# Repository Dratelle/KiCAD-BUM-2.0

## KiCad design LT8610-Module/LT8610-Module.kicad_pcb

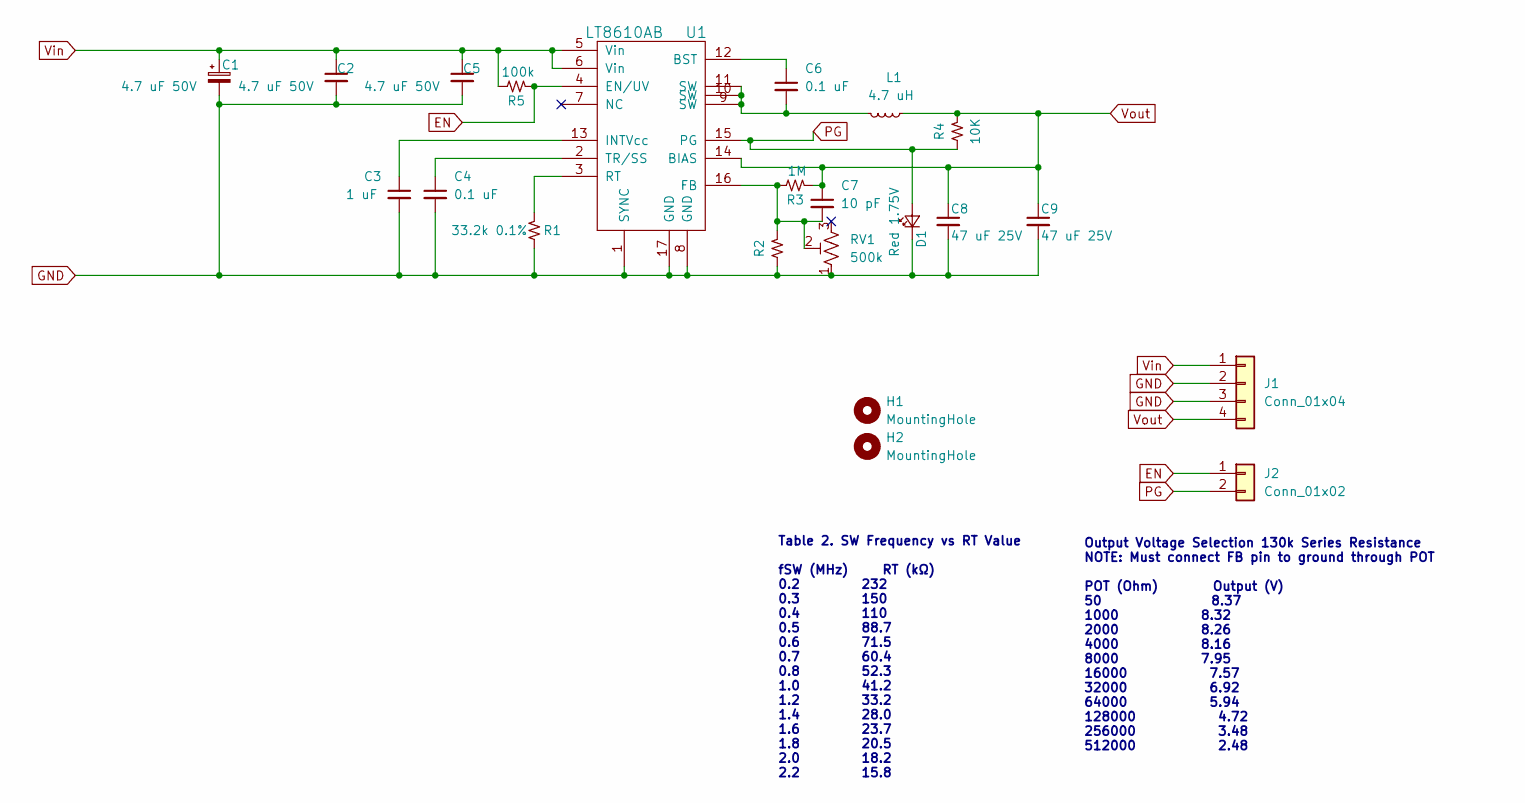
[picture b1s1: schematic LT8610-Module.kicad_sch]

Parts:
C1: 4.7 uF 50V; CP_Elec_4x5.4; Part Number PCE3931CT-ND
C2, C5: 4.7 uF 50V; C_0805_2012Metric; Part Number 490-GRM21BZ71H475KE15KCT-ND
C3: 1 uF; C_0603_1608Metric; Part Number 13-CC0603KRX6S8BB105CT-ND
C4, C6: 0.1 uF; C_0402_1005Metric; Part Number 445-5933-1-ND
C7: 10 pF; C_0402_1005Metric; Part Number 399-C0402C100K5RAC7867CT-ND
C8, C9: 47 uF 25V; C_1206_3216Metric; Part Number 445-8047-1-ND
D1: Red 1.75V; LED_0402_1005Metric; Part Number 1080-1571-1-ND
H1, H2: MountingHole; MountingHole_2.2mm_M2_ISO7380
J1: Conn_01x04; PinHeader_1x04_P2.54mm_Vertical
J2: Conn_01x02; PinHeader_1x02_P2.54mm_Vertical
L1: 4.7 uH; L_Vishay_IHLP-2020; Part Number 541-1090-1-ND
R1: 33.2k 0.1%; R_0402_1005Metric; Part Number A127465CT-ND
R2: R_0402_1005Metric
R3: 1M; R_0402_1005Metric; Part Number 13-RE0402BRE071MLCT-ND
R4: 10K; R_0402_1005Metric; Part Number TNP10.0KDACT-ND
R5: 100k; R_0402_1005Metric; Part Number A102574CT-ND
RV1: 500k; Potentiometer_Bourns_3214W_Vertical; Part Number 3214W-1-504ECT-ND
U1: LT8610AB; MSOP-16-1EP_3x4mm_P0.5mm_EP1.65x2.85mm_ThermalVias; Part Number LT8610ABHMSE#PBF-ND

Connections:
EN: J2.1, R5.1, U1.4 (EN/UV)
GND: C1.2, C2.2, C3.2, C4.2, C5.2, C8.2, C9.2, D1.1 (K), J1.2, J1.3, R1.2, R2.2, RV1.1, U1.1 (SYNC), U1.8 (GND), U1.17 (GND)
unnamed: C3.1, U1.13 (INTVcc)
unnamed: C4.1, U1.2 (TR/SS)
unnamed: C6.1, U1.12 (BST)
unnamed: C6.2, L1.2, U1.9 (SW), U1.10 (SW), U1.11 (SW)
unnamed: C7.2, R2.1, R3.2, RV1.2, U1.16 (FB)
unnamed: R1.1, U1.3 (RT)
PG: D1.2 (A), J2.2, R4.2, U1.15 (PG)
Vin: C1.1, C2.1, C5.1, J1.1, R5.2, U1.5 (Vin), U1.6 (Vin)
Vout: C7.1, C8.1, C9.1, J1.4, L1.1, R3.1, R4.1, U1.14 (BIAS)

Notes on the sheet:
Table 2. SW Frequency vs RT Value fSW (MHz) RT (kΩ) 0.2 232 0.3 150 0.4 110 0.5 88.7 0.6 71.5 0.7 60.4 0.8 52.3 1.0 41.2 1.2 33.2 1.4 28.0 1.6 23.7 1.8 20.5 2.0 18.2 2.2 15.8
Output Voltage Selection 130k Series Resistance NOTE: Must connect FB pin to ground through POT POT (Ohm) Output (V) 50 8.37 1000 8.32 2000 8.26 4000 8.16 8000 7.95 16000 7.57 32000 6.92 64000 5.94 128000 4.72 256000 3.48 512000 2.48

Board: 4 copper layers, 22 parts (0 on the bottom side), 11 nets, no tracks yet.

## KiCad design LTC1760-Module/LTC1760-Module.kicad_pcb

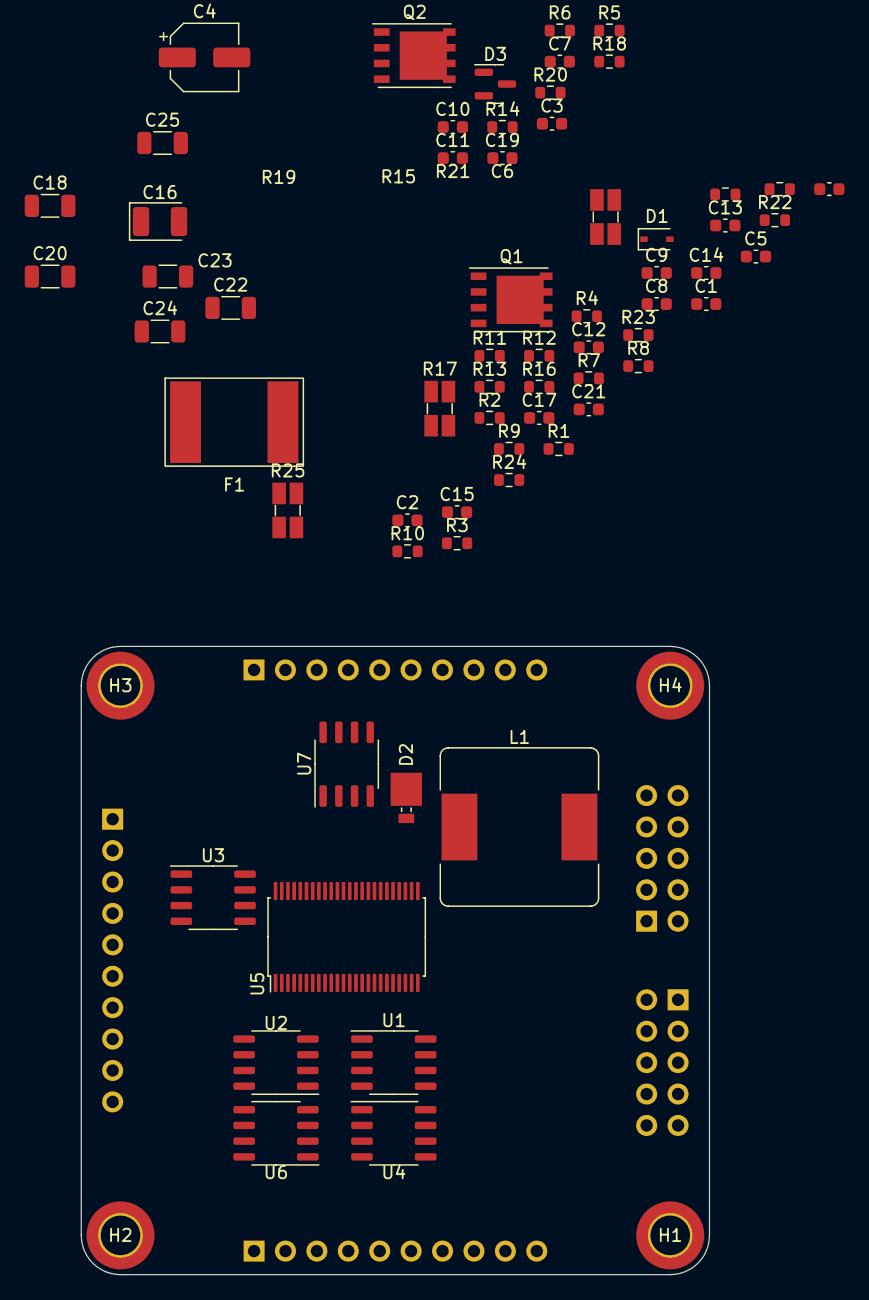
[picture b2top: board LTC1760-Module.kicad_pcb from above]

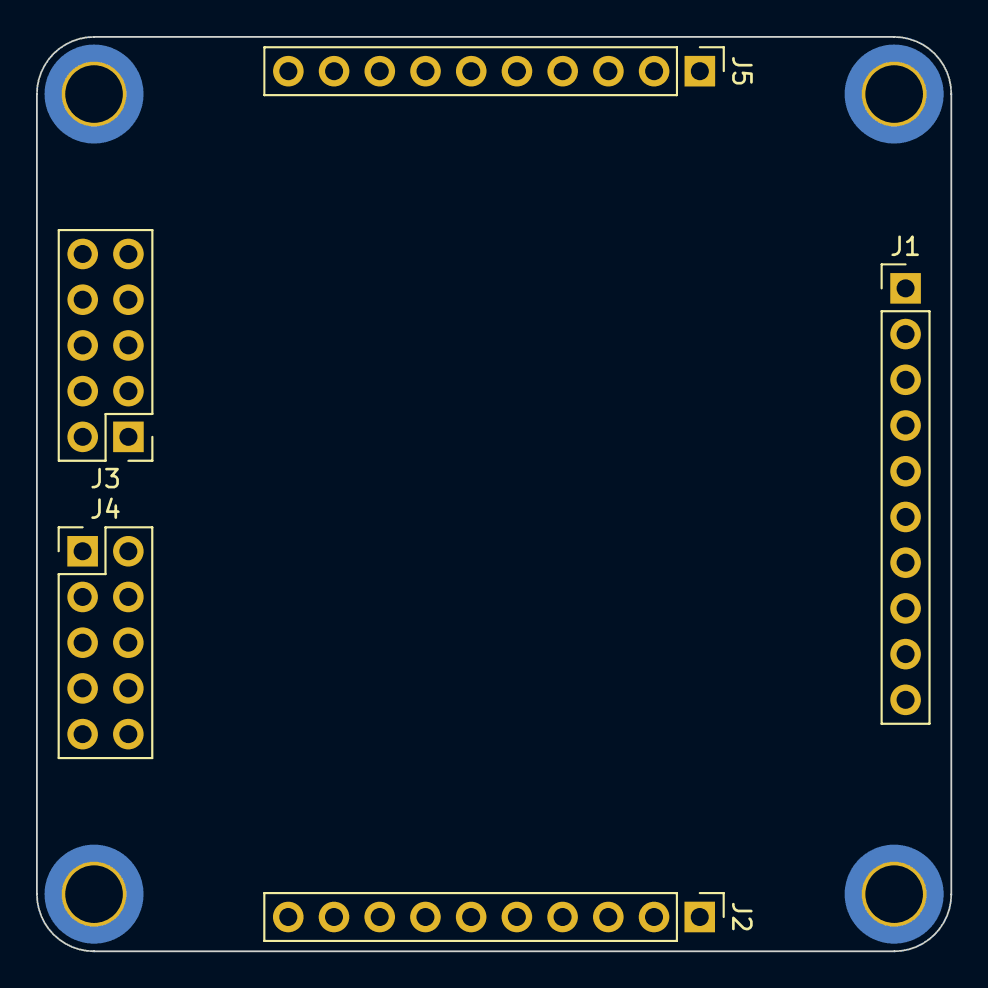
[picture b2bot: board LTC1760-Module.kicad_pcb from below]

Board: 2 copper layers, 50.8 x 50.8 mm, 73 parts (5 on the bottom side), 67 nets, no tracks yet.

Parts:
C1: 0.12uF; C_0603_1608Metric
C2, C8, C21: 100pF; C_0603_1608Metric
C3, C5, C7, C9, C12, C13, C15, C19: 0.1uF; C_0603_1608Metric
C4: 10 uF 50V; CP_Elec_5x5.3
C6: 1uF; C_0603_1608Metric
C10: 0.012uF; C_0603_1608Metric
C11: 1800pF; C_0603_1608Metric
C14: 0.47 uF; C_0603_1608Metric
C16: 4.7uF; CP_EIA-3528-15_AVX-H
C17: 0.22 uF; C_0603_1608Metric
C18, C20, C22, C23, C24, C25: 10uF; C_1206_3216Metric
D1: CMDSH-3; D_SOD-323
D2: MBRM140T3; D_Powermite_AK
D3: BAT54A; SOT-23
F1: 3A 36V; MF-GSMF
H1, H2, H3, H4: MountingHole_Pad; MountingHole_3.2mm_M3_ISO14580_Pad_TopBottom
J1, J2: Battery 1; PinHeader_1x10_P2.54mm_Vertical
J3: Parallel-I/O; PinHeader_2x05_P2.54mm_Vertical
J4: System-I/O; PinHeader_2x05_P2.54mm_Vertical
J5: Power-I/O; PinHeader_1x10_P2.54mm_Vertical
L1: 10 uH; L_Bourns_SRR1260
Q1, Q2: Si7141DP; PowerPAK_SO-8_Single
R1: 3.3k 1%; R_0603_1608Metric
R2, R4, R6: 15k 1%; R_0603_1608Metric
R3: 47 1%; R_0603_1608Metric
R5, R18: 100 1%; R_0603_1608Metric
R7: 1.21k 1%; R_0603_1608Metric
R8: 51k 1%; R_0603_1608Metric
R9: 12.7k 1%; R_0603_1608Metric
R10, R12: 54.9k 1%; R_0603_1608Metric
R11, R13: 1.13k 1%; R_0603_1608Metric
R14: 4.99k 1%; R_0603_1608Metric
R15, R16: 510k 1%; R_0603_1608Metric
R17: 0.033 1%; Ohmite_LVK12_1234
R19: 0.012 1%; Ohmite_LVK12_1234
R20, R22: 34k 1% 0603; R_0603_1608Metric
R21: 10k 1% 0603; R_0603_1608Metric
R23: 1k 1%; R_0603_1608Metric
R24: 280k 1%; R_0603_1608Metric
R25: 0.024 1%; Ohmite_LVK12_1234
U1, U2, U7: FDS6990; SO-8_3.9x4.9mm_P1.27mm
U3, U4, U6: FDS4935BZ; SO-8_3.9x4.9mm_P1.27mm
U5: LTC1760; TSSOP-48_6.1x12.5mm_P0.5mm

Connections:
/CHG_OUT: C24.1, C25.1, R25.4, U1.5 (D), U1.6 (D), U1.7 (D), U1.8 (D)
/CLP: C12.2, J3.6, R14.1, U5.36 (CLP)
/DCDIV: C8.1, J3.5, R7.2, R9.1, U5.16 (DCDIV)
/DCOUT: J5.4, J5.5, J5.6
/DCSUM: R19.4, U3.5 (D), U3.6 (D), U4.5 (D), U4.6 (D), U4.7 (D), U4.8 (D)
/DCSUPPLY: C22.1, C23.1, R17.4, U3.7 (D), U3.8 (D), U7.7 (D), U7.8 (D)
/GND: C1.2, C2.2, C3.2, C4.2, C5.1, C6.2, C7.1, C8.2, C9.2, C10.2, C11.2, C13.1, C14.2, C16.2, C18.2, C19.1, C20.2, C21.2, C22.2, C23.2, C24.2, C25.2, D2.2 (A), H1.1, H2.1, H3.1, H4.1, J1.9, J1.10, J2.9, J2.10, J3.9, J3.10, J4.9, J4.10, J5.7, J5.8, J5.9, J5.10, R7.1, R20.1, R21.1, R22.1, U5.24 (GND), U5.38 (PGND), U7.3 (S)
/ILIMT: R21.2, U5.32 (ILIM)
/INTB: R6.2, U5.29 (INTB)
/LOPWR: C21.1, R20.2, R24.1, U5.12 (LOPWR)
/MODE: C5.2, J3.3, J3.4, R2.1, R3.1, R4.1, R6.1, U5.20 (VDDS), U5.25 (VCC2), U5.26 (MODE)
/SCL: J4.3, R4.2, U5.18 (SCL)
/SCL_B1: J1.3, J1.4, J4.5, U5.19 (SCL_B1)
/SCL_B2: J2.3, J2.4, J4.7, U5.17 (SCL_B2)
/SCN: J3.8, R19.2, U5.4 (SCN)
/SCP: J3.7, R19.3, U5.5 (SCP)
/SDA: J4.4, R2.2, U5.22 (SDA)
/SDA_B1: J1.5, J1.6, J4.6, U5.23 (SDA_B1)
/SDA_B2: J2.5, J2.6, J4.8, U5.21 (SDA_B2)
/TH1A: R11.2, U5.30 (TH1A)
/TH1B: R10.2, U5.31 (TH1B)
/TH2A: R13.2, U5.28 (TH2A)
/TH2B: R12.2, U5.27 (TH2B)
/VCC: C16.1, C19.2, D1.2 (A), J3.2, R3.2, R23.2, U5.40 (VCC)
/VLIM: R22.2, U5.33 (VLIM)
/VPLUS: C6.1, J3.1, R5.2
/V_B1: D3.1, Q1.5 (D), U2.7 (D), U2.8 (D), U5.3 (BAT1), U6.5 (D), U6.6 (D)
/V_B2: D3.2, Q2.5 (D), U2.5 (D), U2.6 (D), U5.2 (BAT2), U6.7 (D), U6.8 (D)
/Vin: C4.1, C7.2, J5.1, J5.2, J5.3, R9.2, R17.1
/~BAT_EN1: J4.1, J4.2, Q1.4 (G), R15.2
/~BAT_EN2: Q2.4 (G), R16.2
unnamed: C1.1, R1.2
unnamed: C2.1, R1.1, U5.14 (ITH)
unnamed: C3.1, U5.15 (ISET)
unnamed: C9.1, R5.1, U5.1 (VPLUS)
unnamed: C10.1, R8.2
unnamed: C11.1, R8.1, U5.37 (COMP1)
unnamed: C12.1, C13.2, R17.3, U5.41 (DCIN)
unnamed: C14.1, C15.2, U5.13 (VSET)
unnamed: C15.1, R18.2
unnamed: C17.1, D2.1 (K), L1.1, U5.42 (SW), U7.1 (S), U7.5 (D), U7.6 (D)
unnamed: C17.2, D1.1 (K), U5.43 (BOOST)
unnamed: C18.1, C20.1, F1.1, R19.1, R24.2
unnamed: D3.3, R23.1
unnamed: L1.2, R25.1
unnamed: J1.1, J1.2, Q1.1 (S), Q1.2 (S), Q1.3 (S), R15.1
unnamed: J2.1, J2.2, Q2.1 (S), Q2.2 (S), Q2.3 (S), R16.1
unnamed: J1.7, J1.8, R10.1, R11.1
unnamed: J2.7, J2.8, R12.1, R13.1
unnamed: R14.2, R17.2
unnamed: R18.1, R25.3, U5.34 (CSN)
unnamed: R25.2, U5.35 (CSP)
unnamed: U3.1 (S), U3.3 (S)
unnamed: U3.4 (G), U5.6 (GDCO)
unnamed: U3.2 (G), U5.7 (GDCI)
unnamed: U4.2 (G), U5.8 (GB1O)
unnamed: U5.9 (GB1I), U6.4 (G)
unnamed: U4.4 (G), U5.10 (GB2O)
unnamed: U5.11 (GB2I), U6.2 (G)
unnamed: U5.39 (BGATE), U7.4 (G)
unnamed: U5.44 (TGATE), U7.2 (G)
unnamed: U1.3 (S), U2.1 (S), U5.45 (SHC1)
unnamed: U1.4 (G), U2.2 (G), U5.46 (GHC1)
unnamed: U1.2 (G), U2.4 (G), U5.47 (GHC2)
unnamed: U1.1 (S), U2.3 (S), U5.48 (SHC2)
unnamed: U4.3 (S), U6.1 (S)
unnamed: U4.1 (S), U6.3 (S)

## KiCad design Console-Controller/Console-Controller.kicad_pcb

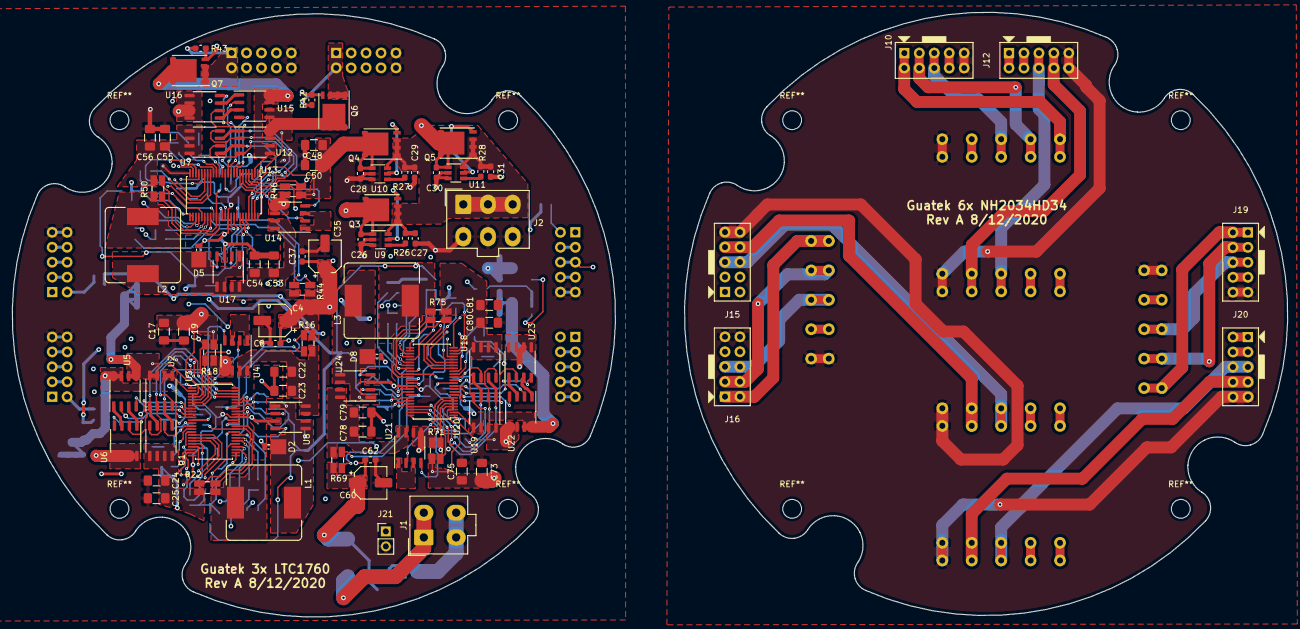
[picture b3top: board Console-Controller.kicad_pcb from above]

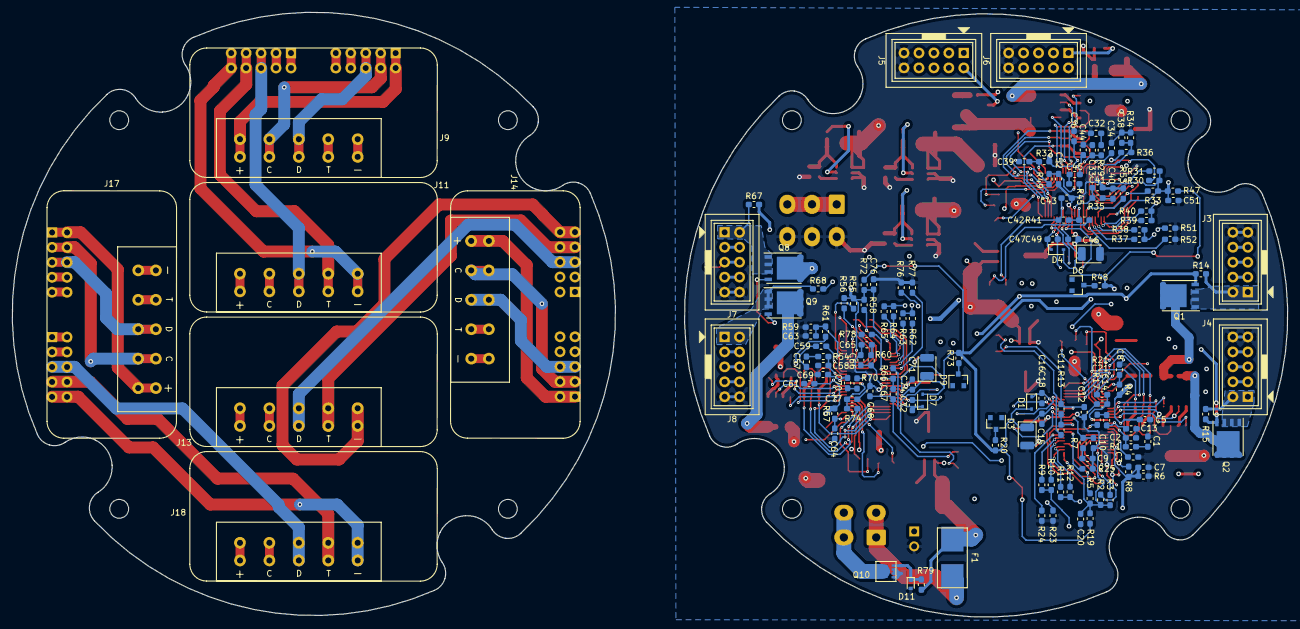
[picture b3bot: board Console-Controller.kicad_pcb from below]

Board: 4 copper layers, 102.5 x 102.5 mm, 229 parts (141 on the bottom side), 210 nets.

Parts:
C1, C32, C57: 0.12uF; C_0603_1608Metric_Pad1.05x0.95mm_HandSolder
C2, C7, C21, C33, C38, C52, C58, C63, C77: 100pF; C_0603_1608Metric_Pad1.05x0.95mm_HandSolder
C3, C6, C8, C11, C12, C14, C18, C20, C34, C37, C39, C42, C43, C45, C49, C51, C59, C62, C64, C67, C68, C70, C74, C76: 0.1uF; C_0603_1608Metric_Pad1.05x0.95mm_HandSolder
C4, C35, C60: 10 uF 50V; CP_Elec_5x5.3
C5, C36, C61: 1uF; C_0603_1608Metric_Pad1.05x0.95mm_HandSolder
C9, C40, C65: 0.012uF; C_0603_1608Metric_Pad1.05x0.95mm_HandSolder
C10, C41, C66: 1800pF; C_0603_1608Metric_Pad1.05x0.95mm_HandSolder
C13, C44, C69: 0.47 uF; C_0603_1608Metric_Pad1.05x0.95mm_HandSolder
C15, C46, C71: 4.7uF; CP_EIA-3528-15_AVX-H
C16, C47, C72: 0.22 uF; C_0603_1608Metric_Pad1.05x0.95mm_HandSolder
C17, C19, C22, C23, C24, C25, C48, C50, C53, C54, C55, C56, C73, C75, C78, C79, C80, C81: 10uF; C_1206_3216Metric_Pad1.42x1.75mm_HandSolder
C26, C27, C28, C29, C30, C31: 0.1 uF 50V; C_0603_1608Metric_Pad1.05x0.95mm_HandSolder
D1, D4, D7: CMDSH-3; D_SOD-323
D2, D5, D8: MBRM140T3; D_Powermite_AK
D3, D6, D9: BAT54A; SOT-23
D11: BZT52C20T-7; D_SOD-523
F1: 10 A; 01550900M
J1: Charge Input; Molex_Mini-Fit_Jr_5566-04A_2x02_P4.20mm_Vertical
J2: Battery Output; Molex_Mini-Fit_Jr_5566-06A_2x03_P4.20mm_Vertical
J3, J4, J5, J6, J7, J8: Battery; SAM10310-ND
J9, J11, J13, J14, J17, J18: Battery In; NH2034HD34
J10, J12, J15, J16, J19, J20: Battery Out; SAM11936-ND
J21: BATT_EN; PinHeader_1x02_P2.54mm_Vertical
L1, L2, L3: 10 uH; L_Bourns_SRR1260
Q1, Q2, Q6, Q7, Q8, Q9: Si7141DP; PowerPAK_SO-8_Single
Q3, Q4, Q5: Si7463DP; PowerPAK_SO-8_Single
Q10: SiSA72DN; PowerPAK 1212
R1, R29, R54: 3.3k 1%; R_0603_1608Metric_Pad1.05x0.95mm_HandSolder
R2, R3, R5, R30, R31, R33, R55, R56, R58: 15k 1%; R_0603_1608Metric_Pad1.05x0.95mm_HandSolder
R4, R17, R32, R45, R57, R70: 100 1%; R_0603_1608Metric_Pad1.05x0.95mm_HandSolder
R6, R34, R59: 1.21k 1%; R_0603_1608Metric_Pad1.05x0.95mm_HandSolder
R7, R35, R60: 51k 1%; R_0603_1608Metric_Pad1.05x0.95mm_HandSolder
R8, R36, R61: 12.7k 1%; R_0603_1608Metric_Pad1.05x0.95mm_HandSolder
R9, R11, R37, R39, R62, R64: 54.9k 1%; R_0603_1608Metric_Pad1.05x0.95mm_HandSolder
R10, R12, R38, R40, R63, R65: 1.13k 1%; R_0603_1608Metric_Pad1.05x0.95mm_HandSolder
R13, R41, R66: 4.99k 1%; R_0603_1608Metric_Pad1.05x0.95mm_HandSolder
R14, R15, R42, R43, R67, R68: 510k 1%; R_0603_1608Metric_Pad1.05x0.95mm_HandSolder
R16, R44, R69: 0.033 1%; Ohmite_LVK12_1234
R18, R46, R71: 0.012 1%; Ohmite_LVK12_1234
R19, R47, R72: 47 1%; R_0603_1608Metric_Pad1.05x0.95mm_HandSolder
R20, R48, R73: 1k 1%; R_0603_1608Metric_Pad1.05x0.95mm_HandSolder
R21, R49, R74: 280k 1%; R_0603_1608Metric_Pad1.05x0.95mm_HandSolder
R22, R50, R75: 0.024 1%; Ohmite_LVK12_1234
R23, R25, R51, R53, R76, R78: 34k 1% 0603; R_0603_1608Metric_Pad1.05x0.95mm_HandSolder
R24, R52, R77: 10k 1% 0603; R_0603_1608Metric_Pad1.05x0.95mm_HandSolder
R26, R27, R28: 470k; R_0603_1608Metric_Pad1.05x0.95mm_HandSolder
R79: 10K; R_0603_1608Metric_Pad1.05x0.95mm_HandSolder
U1, U2, U7, U8, U12, U17, U18, U19, U24: FDS6990; SO-8_3.9x4.9mm_P1.27mm
U3, U13, U20: LTC1760; TSSOP-48_6.1x12.5mm_P0.5mm
U4, U5, U6, U14, U15, U16, U21, U22, U23: FDS4935BZ; SO-8_3.9x4.9mm_P1.27mm
U9, U10, U11: LTC4412HVIS6; TSOT-23-6

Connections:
/GND: C1.2, C2.2, C3.2, C4.2, C5.2, C6.1, C7.2, C8.2, C9.2, C10.2, C12.1, C13.2, C15.2, C17.2, C18.1, C19.2, C20.1, C21.2, C22.2, C23.2, C24.2, C25.2, C26.2, C27.2, C28.2, C29.2, C30.2, C31.2, C32.2, C33.2, C34.2, C35.2, C36.2, C37.1, C38.2, C39.2, C40.2, C41.2, C43.1, C44.2, C46.2, C48.2, C49.1, C50.2, C51.1, C52.2, C53.2, C54.2, C55.2, C56.2, C57.2, C58.2, C59.2, C60.2, C61.2, C62.1, C63.2, C64.2, C65.2, C66.2, C68.1, C69.2, C71.2, C73.2, C74.1, C75.2, C76.1, C77.2, C78.2, C79.2, C80.2, C81.2, D2.2, D5.2, D8.2, D11.2, J2.4, J2.5, J2.6, J3.9, J3.10, J4.9, J4.10, J5.9, J5.10, J6.9, J6.10, J7.9, J7.10, J8.9, J8.10, J21.2, Q10.1, Q10.2, Q10.3, R6.1, R23.1, R24.1, R25.1, R34.1, R51.1, R52.1, R53.1, R59.1, R76.1, R77.1, R78.1, U3.24, U3.38, U8.3, U9.2, U9.3, U10.2, U10.3, U11.2, U11.3, U13.24, U13.38, U17.3, U20.24, U20.38, U24.3
/LTC1670_C/CHG_OUT: C80.1, C81.1, R75.4, U18.5, U18.6, U18.7, U18.8
/LTC1670_C/CLP: C11.2, C42.2, C67.2, R13.1, R41.1, R66.1, U3.36, U13.36, U20.36
/LTC1670_C/DCDIV: C7.1, C38.1, C63.1, R6.2, R8.1, R34.2, R36.1, R59.2, R61.1, U3.16, U13.16, U20.16
/LTC1670_C/DCOUT: C30.1, C73.1, C75.1, Q5.5, R71.1, R74.2, U11.1
/LTC1670_C/DCSUM: R71.4, U21.5, U21.6, U23.5, U23.6, U23.7, U23.8
/LTC1670_C/DCSUPPLY: C78.1, C79.1, R69.4, U21.7, U21.8, U24.7, U24.8
/LTC1670_C/ILIMT: R77.2, U20.32
/LTC1670_C/INTB: R58.2, U20.29
/LTC1670_C/LOPWR: C77.1, R74.1, R76.2, U20.12
/LTC1670_C/MODE: C20.2, C51.2, C76.2, R2.1, R3.1, R5.1, R19.1, R30.1, R31.1, R33.1, R47.1, R55.1, R56.1, R58.1, R72.1, U3.20, U3.25, U3.26, U13.20, U13.25, U13.26, U20.20, U20.25, U20.26
/LTC1670_C/SCL: R56.2, U20.18
/LTC1670_C/SCL_B1: J7.3, J7.4, U20.19
/LTC1670_C/SCL_B2: J8.3, J8.4, U20.17
/LTC1670_C/SCN: R18.2, R46.2, R71.2, U3.4, U13.4, U20.4
/LTC1670_C/SCP: R18.3, R46.3, R71.3, U3.5, U13.5, U20.5
/LTC1670_C/SDA: R55.2, U20.22
/LTC1670_C/SDA_B1: J7.5, J7.6, U20.23
/LTC1670_C/SDA_B2: J8.5, J8.6, U20.21
/LTC1670_C/TH1A: R63.2, U20.30
/LTC1670_C/TH1B: R62.2, U20.31
/LTC1670_C/TH2A: R65.2, U20.28
/LTC1670_C/TH2B: R64.2, U20.27
/LTC1670_C/VCC: C15.1, C18.2, C46.1, C49.2, C71.1, C74.2, D1.2, D4.2, D7.2, R19.2, R20.2, R47.2, R48.2, R72.2, R73.2, U3.40, U13.40, U20.40
/LTC1670_C/VLIM: R78.2, U20.33
/LTC1670_C/VPLUS: C5.1, C36.1, C61.1, R4.2, R32.2, R57.2
/LTC1670_C/Vin: C4.1, C6.2, C35.1, C37.2, C60.1, C62.2, F1.2, R8.2, R16.1, R36.2, R44.1, R61.2, R69.1, R79.1
/LTC1670_C/~BAT_EN: J21.1, Q1.4, Q2.4, Q6.4, Q7.4, Q8.4, Q9.4, R14.2, R15.2, R42.2, R43.2, R67.2, R68.2
/LTC1760_A/CHG_OUT: C24.1, C25.1, R22.4, U1.5, U1.6, U1.7, U1.8
/LTC1760_A/DCOUT: C17.1, C19.1, C26.1, Q3.5, R18.1, R21.2, U9.1
/LTC1760_A/DCSUM: R18.4, U4.5, U4.6, U6.5, U6.6, U6.7, U6.8
/LTC1760_A/DCSUPPLY: C22.1, C23.1, R16.4, U4.7, U4.8, U8.7, U8.8
/LTC1760_A/ILIMT: R24.2, U3.32
/LTC1760_A/INTB: R5.2, U3.29
/LTC1760_A/LOPWR: C21.1, R21.1, R23.2, U3.12
/LTC1760_A/SCL: R3.2, U3.18
/LTC1760_A/SCL_B1: J3.3, J3.4, U3.19
/LTC1760_A/SCL_B2: J4.3, J4.4, U3.17
/LTC1760_A/SDA: R2.2, U3.22
/LTC1760_A/SDA_B1: J3.5, J3.6, U3.23
/LTC1760_A/SDA_B2: J4.5, J4.6, U3.21
/LTC1760_A/TH1A: R10.2, U3.30
/LTC1760_A/TH1B: R9.2, U3.31
/LTC1760_A/TH2A: R12.2, U3.28
/LTC1760_A/TH2B: R11.2, U3.27
/LTC1760_A/VLIM: R25.2, U3.33
/LTC1760_B/CHG_OUT: C55.1, C56.1, R50.4, U7.5, U7.6, U7.7, U7.8
/LTC1760_B/DCOUT: C28.1, C48.1, C50.1, Q4.5, R46.1, R49.2, U10.1
/LTC1760_B/DCSUM: R46.4, U14.5, U14.6, U16.5, U16.6, U16.7, U16.8
/LTC1760_B/DCSUPPLY: C53.1, C54.1, R44.4, U14.7, U14.8, U17.7, U17.8
/LTC1760_B/ILIMT: R52.2, U13.32
/LTC1760_B/INTB: R33.2, U13.29
/LTC1760_B/LOPWR: C52.1, R49.1, R51.2, U13.12
/LTC1760_B/SCL: R31.2, U13.18
/LTC1760_B/SCL_B1: J5.3, J5.4, U13.19
/LTC1760_B/SCL_B2: J6.3, J6.4, U13.17
/LTC1760_B/SDA: R30.2, U13.22
/LTC1760_B/SDA_B1: J5.5, J5.6, U13.23
/LTC1760_B/SDA_B2: J6.5, J6.6, U13.21
/LTC1760_B/TH1A: R38.2, U13.30
/LTC1760_B/TH1B: R37.2, U13.31
/LTC1760_B/TH2A: R40.2, U13.28
/LTC1760_B/TH2B: R39.2, U13.27
/LTC1760_B/VLIM: R53.2, U13.33
/sheet6090344F/Vout: C27.1, C29.1, C31.1, J2.1, J2.2, J2.3, Q3.1, Q3.2, Q3.3, Q4.1, Q4.2, Q4.3, Q5.1, Q5.2, Q5.3, R26.1, R27.1, R28.1, U9.6, U10.6, U11.6
GNDREF: J1.3, J1.4, Q10.5
unnamed: C1.1, R1.2
unnamed: C2.1, R1.1, U3.14
unnamed: C3.1, U3.15
unnamed: C8.1, R4.1, U3.1
unnamed: C9.1, R7.2
unnamed: C10.1, R7.1, U3.37
unnamed: C11.1, C12.2, R16.3, U3.41
unnamed: C13.1, C14.2, U3.13
unnamed: C14.1, R17.2
unnamed: C16.1, D2.1, L1.1, U3.42, U8.1, U8.5, U8.6
unnamed: C16.2, D1.1, U3.43
unnamed: C32.1, R29.2
unnamed: C33.1, R29.1, U13.14
unnamed: C34.1, U13.15
unnamed: C39.1, R32.1, U13.1
unnamed: C40.1, R35.2
unnamed: C41.1, R35.1, U13.37
unnamed: C42.1, C43.2, R44.3, U13.41
unnamed: C44.1, C45.2, U13.13
unnamed: C45.1, R45.2
unnamed: C47.1, D5.1, L2.1, U13.42, U17.1, U17.5, U17.6
unnamed: C47.2, D4.1, U13.43
unnamed: C57.1, R54.2
unnamed: C58.1, R54.1, U20.14
unnamed: C59.1, U20.15
unnamed: C64.1, R57.1, U20.1
unnamed: C65.1, R60.2
unnamed: C66.1, R60.1, U20.37
unnamed: C67.1, C68.2, R69.3, U20.41
unnamed: C69.1, C70.2, U20.13
unnamed: C70.1, R70.2
unnamed: C72.1, D8.1, L3.1, U20.42, U24.1, U24.5, U24.6
unnamed: C72.2, D7.1, U20.43
unnamed: D3.3, R20.1
unnamed: D6.3, R48.1
unnamed: D9.3, R73.1
unnamed: D11.1, Q10.4, R79.2
unnamed: F1.1, J1.1, J1.2
unnamed: J3.1, J3.2, Q1.1, Q1.2, Q1.3, R14.1
unnamed: J3.7, J3.8, R9.1, R10.1
unnamed: J4.1, J4.2, Q2.1, Q2.2, Q2.3, R15.1
unnamed: J4.7, J4.8, R11.1, R12.1
unnamed: J5.1, J5.2, Q6.1, Q6.2, Q6.3, R42.1
unnamed: J5.7, J5.8, R37.1, R38.1
unnamed: J6.1, J6.2, Q7.1, Q7.2, Q7.3, R43.1
unnamed: J6.7, J6.8, R39.1, R40.1
unnamed: J7.1, J7.2, Q8.1, Q8.2, Q8.3, R67.1
unnamed: J7.7, J7.8, R62.1, R63.1
unnamed: J8.1, J8.2, Q9.1, Q9.2, Q9.3, R68.1
unnamed: J8.7, J8.8, R64.1, R65.1
unnamed: J9.1, J9.2, J10.1, J10.2
unnamed: J9.3, J9.4, J10.3, J10.4
unnamed: J9.5, J9.6, J10.5, J10.6
unnamed: J9.7, J9.8, J10.7, J10.8
unnamed: J9.9, J9.10, J10.9, J10.10, J11.9, J11.10, J12.9, J12.10, J13.9, J13.10, J14.9, J14.10, J15.9, J15.10, J16.9, J16.10, J17.9, J17.10, J18.9, J18.10, J19.9, J19.10, J20.9, J20.10
unnamed: J11.1, J11.2, J12.1, J12.2
unnamed: J11.3, J11.4, J12.3, J12.4
unnamed: J11.5, J11.6, J12.5, J12.6
unnamed: J11.7, J11.8, J12.7, J12.8
unnamed: J13.1, J13.2, J15.1, J15.2
unnamed: J13.3, J13.4, J15.3, J15.4
unnamed: J13.5, J13.6, J15.5, J15.6
unnamed: J13.7, J13.8, J15.7, J15.8
unnamed: J14.1, J14.2, J16.1, J16.2
unnamed: J14.3, J14.4, J16.3, J16.4
unnamed: J14.5, J14.6, J16.5, J16.6
unnamed: J14.7, J14.8, J16.7, J16.8
unnamed: J17.1, J17.2, J19.1, J19.2
unnamed: J17.3, J17.4, J19.3, J19.4
unnamed: J17.5, J17.6, J19.5, J19.6
unnamed: J17.7, J17.8, J19.7, J19.8
unnamed: J18.1, J18.2, J20.1, J20.2
unnamed: J18.3, J18.4, J20.3, J20.4
unnamed: J18.5, J18.6, J20.5, J20.6
unnamed: J18.7, J18.8, J20.7, J20.8
unnamed: L1.2, R22.1
unnamed: L2.2, R50.1
unnamed: L3.2, R75.1
unnamed: Q1.5, U2.7, U2.8, U3.3, U5.5, U5.6
unnamed: Q2.5, U2.5, U2.6, U3.2, U5.7, U5.8
unnamed: Q3.4, U9.5
unnamed: Q4.4, U10.5
unnamed: Q5.4, U11.5
unnamed: Q6.5, U12.7, U12.8, U13.3, U15.5, U15.6
unnamed: Q7.5, U12.5, U12.6, U13.2, U15.7, U15.8
unnamed: Q8.5, U19.7, U19.8, U20.3, U22.5, U22.6
unnamed: Q9.5, U19.5, U19.6, U20.2, U22.7, U22.8
unnamed: R13.2, R16.2
unnamed: R17.1, R22.3, U3.34
unnamed: R22.2, U3.35
unnamed: R26.2, U9.4
unnamed: R27.2, U10.4
unnamed: R28.2, U11.4
unnamed: R41.2, R44.2
unnamed: R45.1, R50.3, U13.34
unnamed: R50.2, U13.35
unnamed: R66.2, R69.2
unnamed: R70.1, R75.3, U20.34
unnamed: R75.2, U20.35
unnamed: U1.1, U2.3, U3.48
unnamed: U1.2, U2.4, U3.47
unnamed: U1.3, U2.1, U3.45
unnamed: U1.4, U2.2, U3.46
unnamed: U3.6, U4.4
unnamed: U3.7, U4.2
unnamed: U3.8, U6.2
unnamed: U3.9, U5.4
unnamed: U3.10, U6.4
unnamed: U3.11, U5.2
unnamed: U3.39, U8.4
unnamed: U3.44, U8.2
unnamed: U4.1, U4.3
unnamed: U5.1, U6.3
unnamed: U5.3, U6.1
unnamed: U7.3, U12.1, U13.45
unnamed: U7.4, U12.2, U13.46
unnamed: U7.1, U12.3, U13.48
unnamed: U7.2, U12.4, U13.47
unnamed: U13.6, U14.4
unnamed: U13.7, U14.2
unnamed: U13.8, U16.2
unnamed: U13.9, U15.4
unnamed: U13.10, U16.4
unnamed: U13.11, U15.2
unnamed: U13.39, U17.4
unnamed: U13.44, U17.2
unnamed: U14.1, U14.3
unnamed: U15.1, U16.3
unnamed: U15.3, U16.1
unnamed: U18.1, U19.3, U20.48
unnamed: U18.2, U19.4, U20.47
unnamed: U18.3, U19.1, U20.45
unnamed: U18.4, U19.2, U20.46
unnamed: U20.6, U21.4
unnamed: U20.7, U21.2
unnamed: U20.8, U23.2
unnamed: U20.9, U22.4
unnamed: U20.10, U23.4
unnamed: U20.11, U22.2
unnamed: U20.39, U24.4
unnamed: U20.44, U24.2
unnamed: U21.1, U21.3
unnamed: U22.1, U23.3
unnamed: U22.3, U23.1

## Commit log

2022-12-14 initial import from Dual-Mag battery design
2022-12-14 fixed bug in LTC1760 full-discharge rechrage mode, missing V_Batt
2022-12-16 added polyfuse to LTC1760 output
2023-02-04 latest WIP, LTC1760 module ready for layout, strone-controller ready for layout but needs mech board drawings
2023-02-06 slight updates to LTC1670 modules (2 resistors added) finalizing console controller and strobe controller
2024-12-14 Initial upload
2025-01-07 Update gitignore
